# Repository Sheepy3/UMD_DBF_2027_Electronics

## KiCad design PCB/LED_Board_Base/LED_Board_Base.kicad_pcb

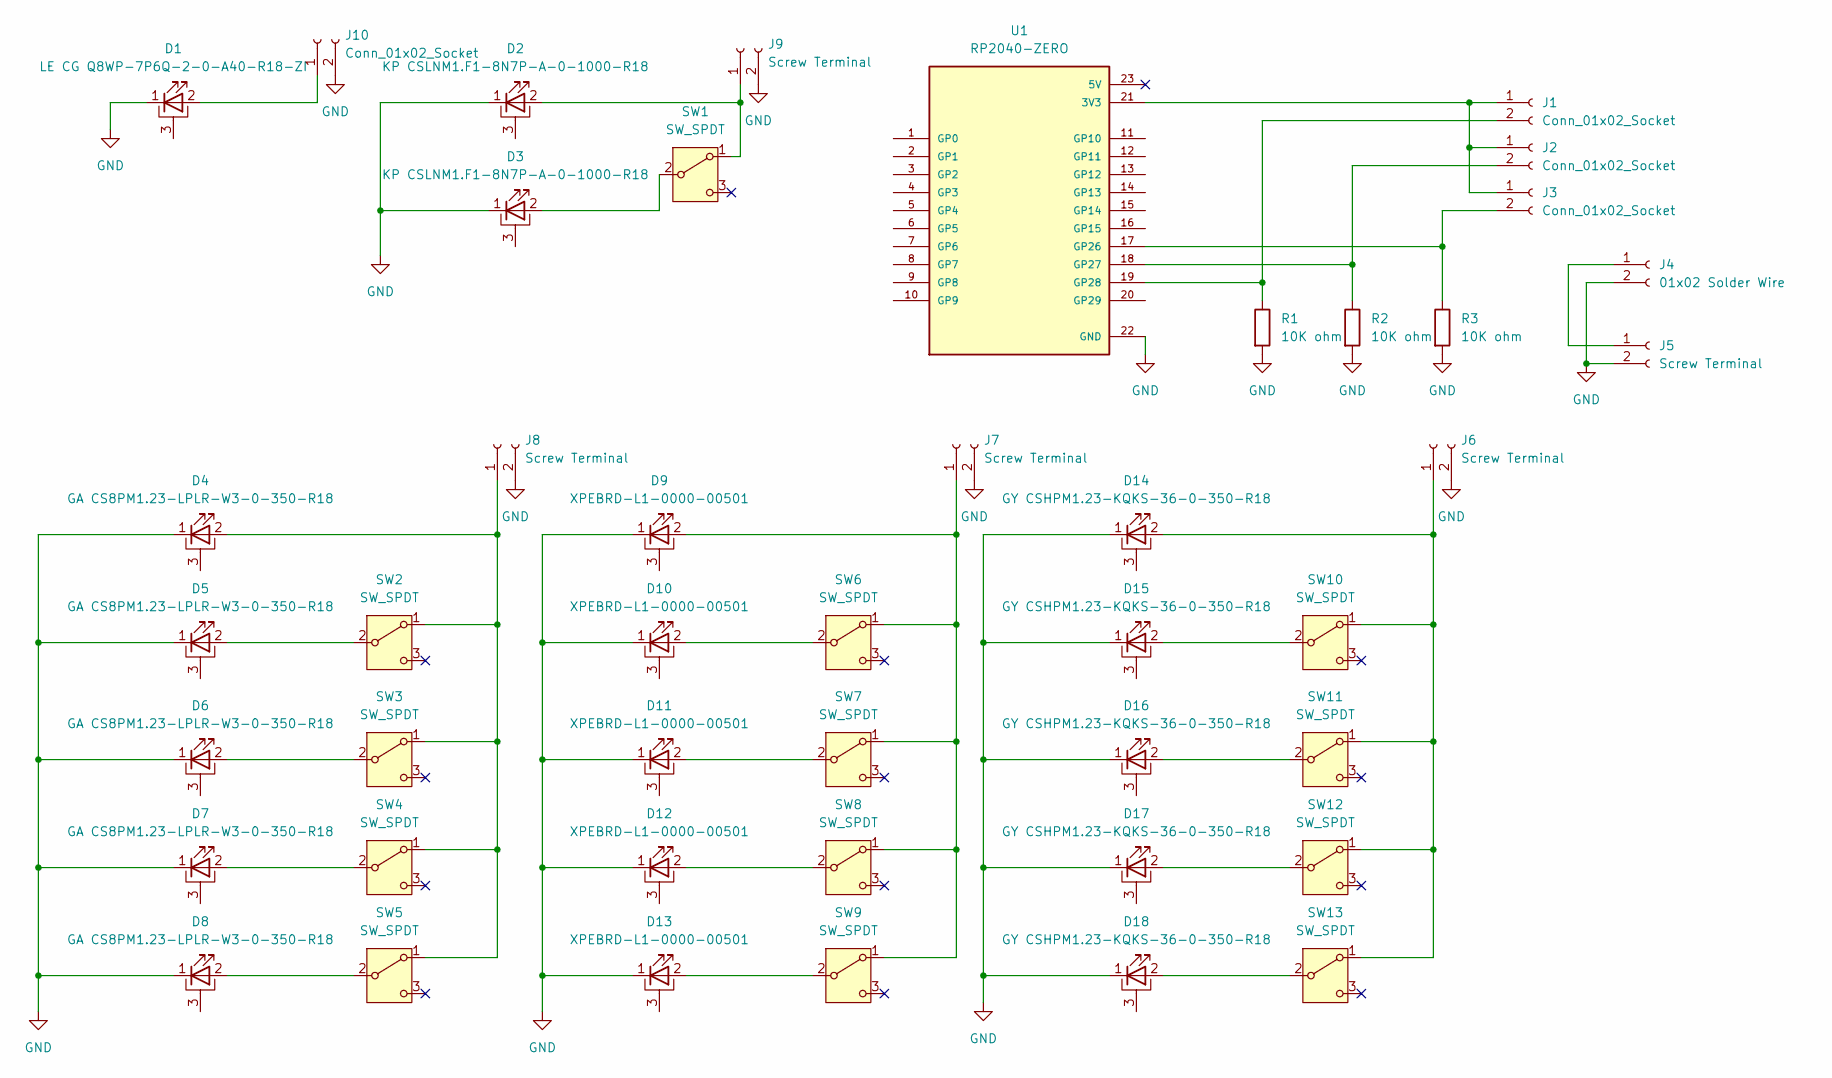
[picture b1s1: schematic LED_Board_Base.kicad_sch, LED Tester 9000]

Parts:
D1: LE CG Q8WP-7P6Q-2-0-A40-R18-ZI; LE_CG_Q8WP-7P6Q-2-0-A40-R18-ZI
D2, D3: KP CSLNM1.F1-8N7P-A-0-1000-R18; KP_CSLNM1.F1-8N7P-A-0-1000-R18
D4, D5, D6, D7, D8: GA CS8PM1.23-LPLR-W3-0-350-R18; KP_CSLNM1.F1-8N7P-A-0-1000-R18
D9, D10, D11, D12, D13: XPEBRD-L1-0000-00501
D14, D15, D16, D17, D18: GY CSHPM1.23-KQKS-36-0-350-R18; KP_CSLNM1.F1-8N7P-A-0-1000-R18
J1, J2, J3: Conn_01x02_Socket; SolderWire-0.1sqmm_1x02_P3.6mm_D0.4mm_OD1mm_Relief
J4: 01x02 Solder Wire; SolderWire-1sqmm_1x02_P7.8mm_D1.4mm_OD3.9mm_Relief
J5, J6, J7, J8, J9: Screw Terminal; TerminalBlock_MaiXu_MX126-5.0-02P_1x02_P5.00mm
J10: Conn_01x02_Socket; TerminalBlock_MaiXu_MX126-5.0-02P_1x02_P5.00mm
R1, R2, R3: 10K ohm; R_Axial_DIN0207_L6.3mm_D2.5mm_P7.62mm_Horizontal
SW1, SW2, SW3, SW4, SW5, SW6, SW7, SW8, SW9, SW10, SW11, SW12, SW13: SW_SPDT; 1101A2CQEA
U1: RP2040-ZERO; MODULE_RP2040-ZERO; PARTREV NA

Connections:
GND: D1.1 (K), D2.1 (K), D3.1 (K), D4.1 (K), D5.1 (K), D6.1 (K), D7.1 (K), D8.1 (K), D9.1 (K), D10.1 (K), D11.1 (K), D12.1 (K), D13.1 (K), D14.1 (K), D15.1 (K), D16.1 (K), D17.1 (K), D18.1 (K), J4.2, J5.2, J6.2, J7.2, J8.2, J9.2, J10.2, R1.2, R2.2, R3.2, U1.22 (GND)
unnamed: D1.2 (A), J10.1
unnamed: D2.2 (A), J9.1, SW1.1 (A)
unnamed: D3.2 (A), SW1.2 (B)
unnamed: D4.2 (A), J8.1, SW2.1 (A), SW3.1 (A), SW4.1 (A), SW5.1 (A)
unnamed: D5.2 (A), SW2.2 (B)
unnamed: D6.2 (A), SW3.2 (B)
unnamed: D7.2 (A), SW4.2 (B)
unnamed: D8.2 (A), SW5.2 (B)
unnamed: D9.2 (A), J7.1, SW6.1 (A), SW7.1 (A), SW8.1 (A), SW9.1 (A)
unnamed: D10.2 (A), SW6.2 (B)
unnamed: D11.2 (A), SW7.2 (B)
unnamed: D12.2 (A), SW8.2 (B)
unnamed: D13.2 (A), SW9.2 (B)
unnamed: D14.2 (A), J6.1, SW10.1 (A), SW11.1 (A), SW12.1 (A), SW13.1 (A)
unnamed: D15.2 (A), SW10.2 (B)
unnamed: D16.2 (A), SW11.2 (B)
unnamed: D17.2 (A), SW12.2 (B)
unnamed: D18.2 (A), SW13.2 (B)
unnamed: J1.1, J2.1, J3.1, U1.21 (3V3)
unnamed: J1.2, R1.1, U1.19 (GP28)
unnamed: J2.2, R2.1, U1.18 (GP27)
unnamed: J3.2, R3.1, U1.17 (GP26)
unnamed: J4.1, J5.1

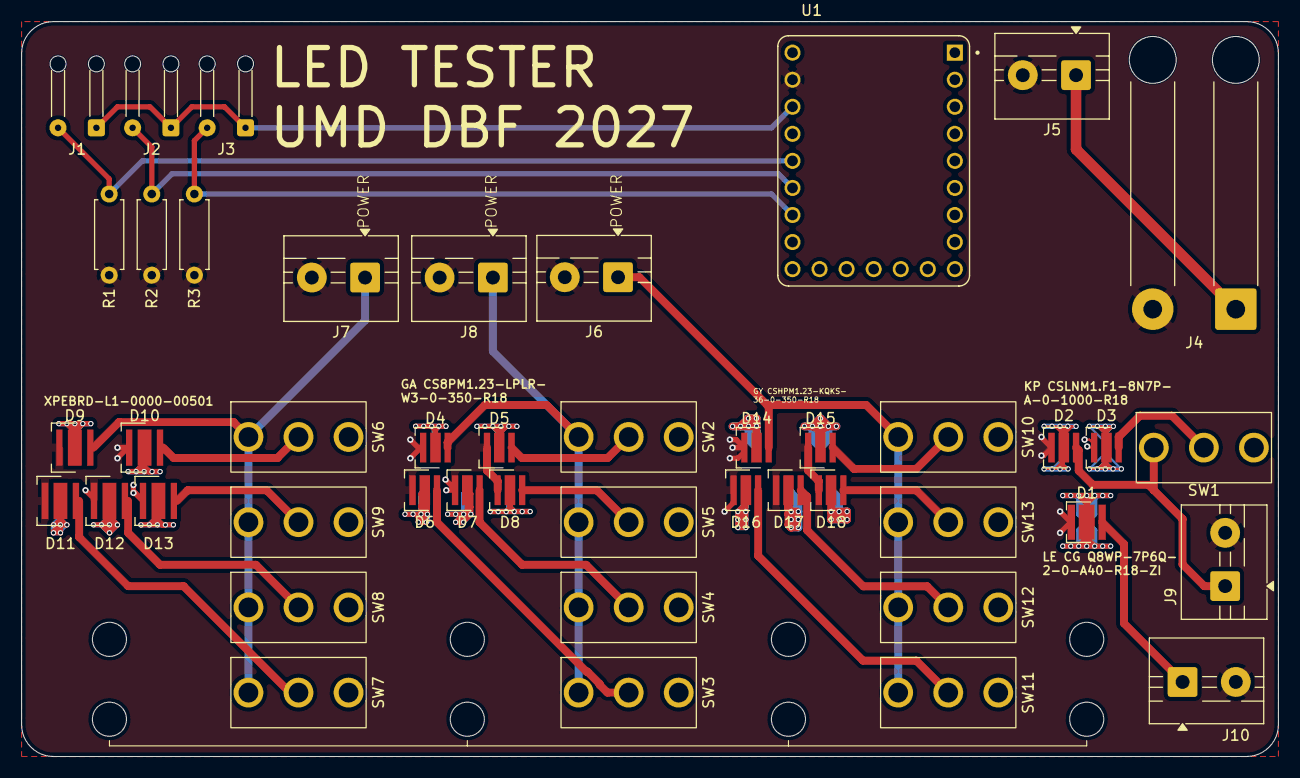
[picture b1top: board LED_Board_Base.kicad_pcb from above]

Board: 2 copper layers, 118.0 x 69.0 mm, 45 parts (0 on the bottom side), 24 nets.

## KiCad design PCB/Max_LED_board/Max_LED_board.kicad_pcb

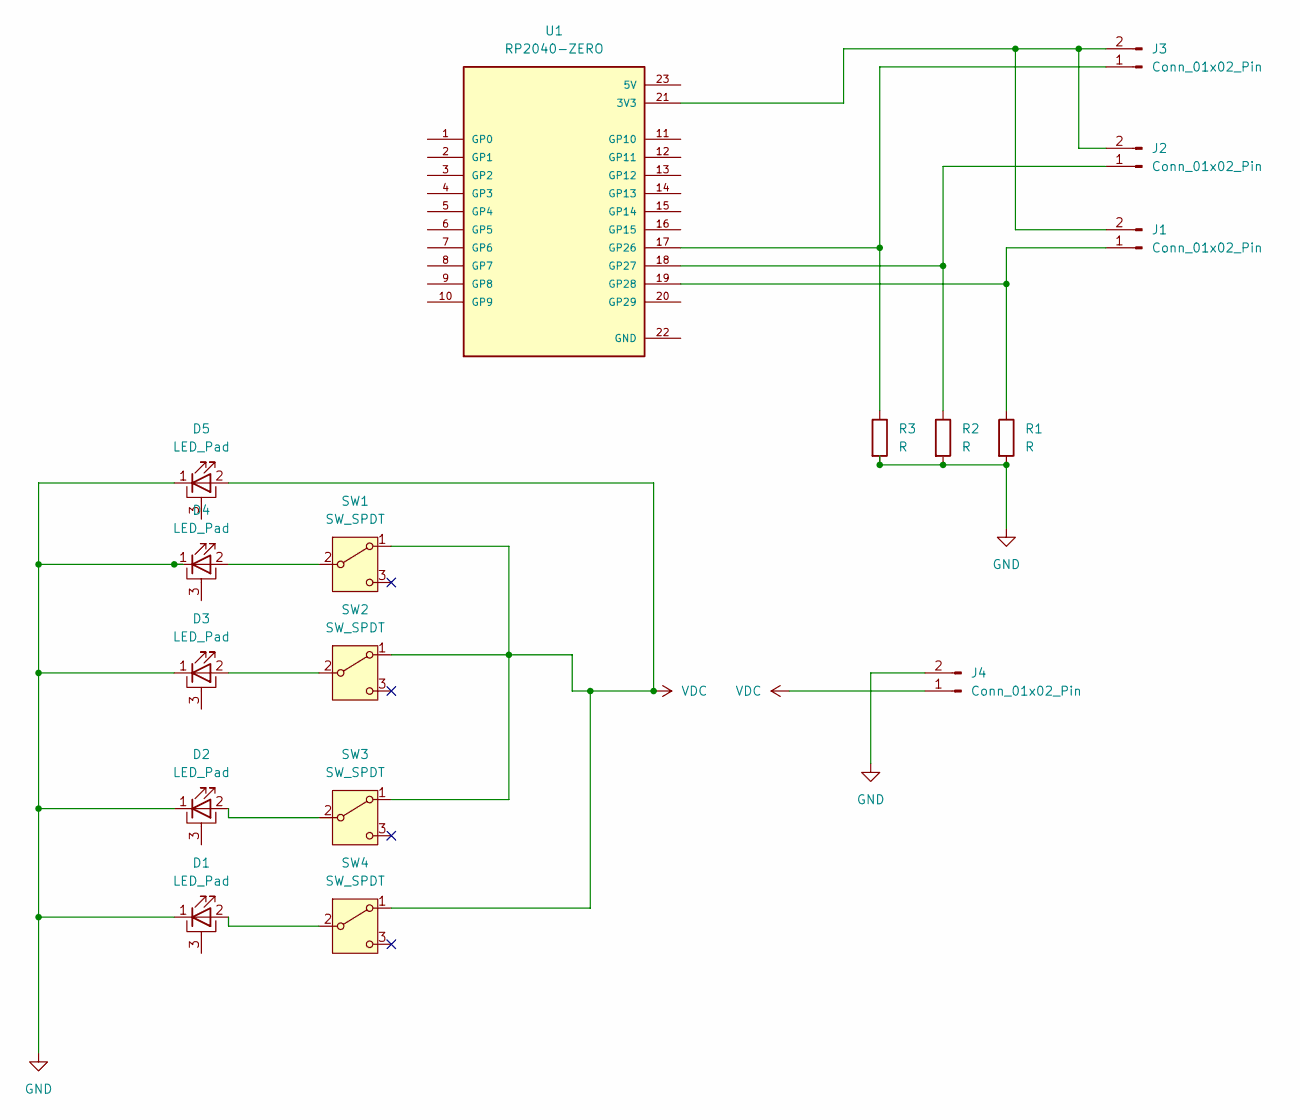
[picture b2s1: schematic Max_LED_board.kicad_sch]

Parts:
D1, D2, D3, D4, D5: LED_Pad; XPEBRD-L1-0000-00501
J1, J2, J3: Conn_01x02_Pin; SolderWire-0.1sqmm_1x02_P3.6mm_D0.4mm_OD1mm_Relief
J4: Conn_01x02_Pin; SolderWire-1sqmm_1x02_P7.8mm_D1.4mm_OD3.9mm_Relief
R1, R2, R3: R; R_Axial_DIN0207_L6.3mm_D2.5mm_P7.62mm_Horizontal
SW1, SW2, SW3, SW4: SW_SPDT; 1101A2CQEA
U1: RP2040-ZERO; MODULE_RP2040-ZERO; PARTREV NA

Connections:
GND: D1.1 (K), D2.1 (K), D3.1 (K), D4.1 (K), D5.1 (K), J4.2, R1.2, R2.2, R3.2
unnamed: D1.2 (A), SW4.2 (B)
unnamed: D2.2 (A), SW3.2 (B)
unnamed: D3.2 (A), SW2.2 (B)
unnamed: D4.2 (A), SW1.2 (B)
unnamed: J1.1, R1.1, U1.19 (GP28)
unnamed: J1.2, J2.2, J3.2, U1.21 (3V3)
unnamed: J2.1, R2.1, U1.18 (GP27)
unnamed: J3.1, R3.1, U1.17 (GP26)
VDC: D5.2 (A), J4.1, SW1.1 (A), SW2.1 (A), SW3.1 (A), SW4.1 (A)

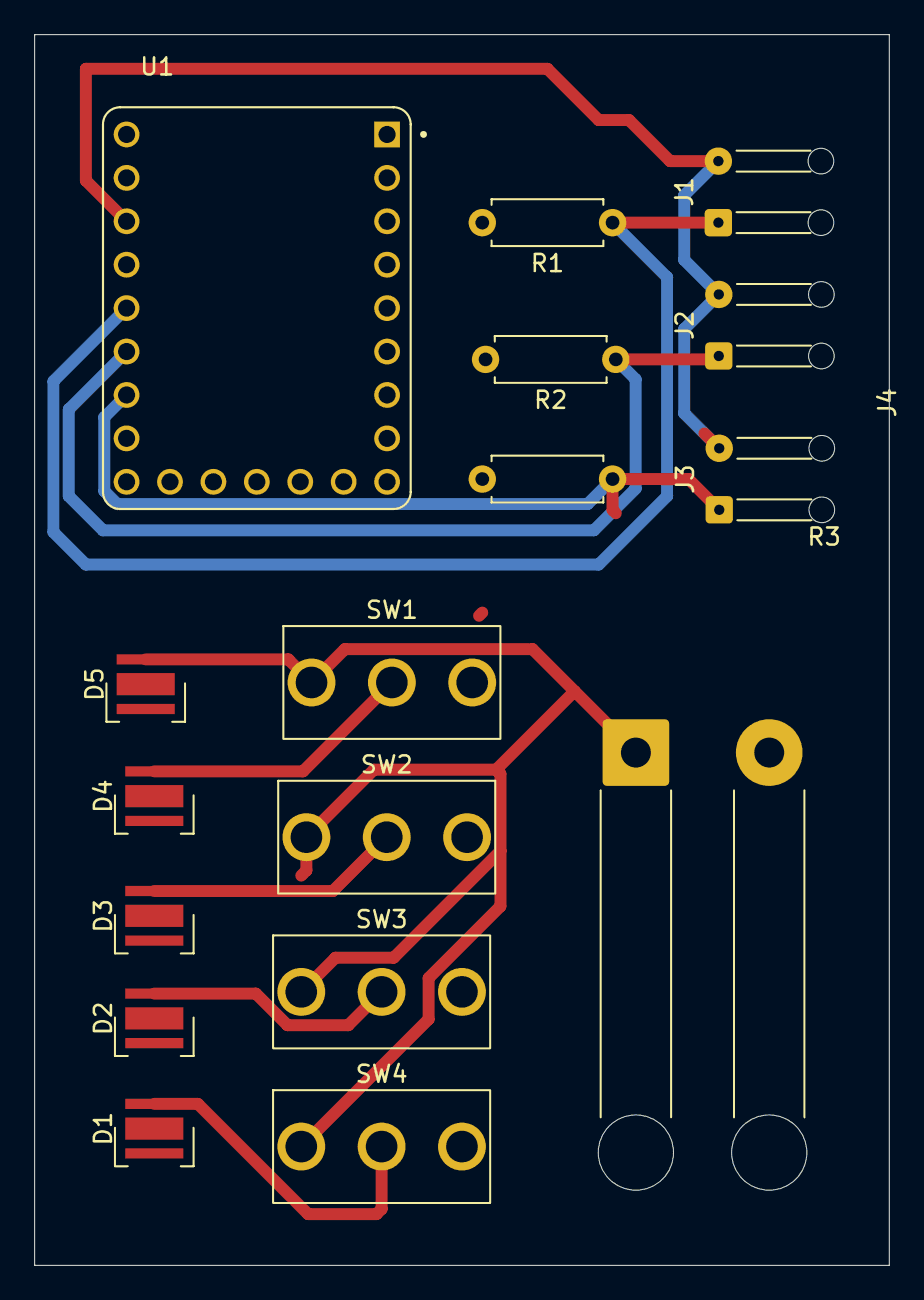
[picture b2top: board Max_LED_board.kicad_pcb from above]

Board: 2 copper layers, 50.0 x 72.0 mm, 17 parts (0 on the bottom side), 10 nets.
